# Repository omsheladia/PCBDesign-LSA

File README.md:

# PCBDesign-LSA
  Behind the Designing of the Line Sensing Array(L.S.A)

## Using kiCAD - Open Source Software
This repository contains hardware design files and datasheets for the Line Sensor Array. This project is still in development and is not ready for release yet.
Coming soon with a finalised touch.

## Features
* Detachable I.C. for easy project based modifications.
* Components can be proctured easily.
* Easy connections for output signals.
* Compact enough to fit into any project.
* Distinguished trace widths for Signal and Power Routes.
 
## Uses
* Obstacle detection on a clear path.
* Line Following.
* Distinguish Colours on a path.

## Components Used
Component | Description
--------- | -----------
LM324 I.C. | Op-Amp I.C.
Photodiode | Absorb light
Resistor | Limit Current
LED | Emit Light
FRC Connector | Connect PCB with other circuits
14 Pin I.C. Socket | Plug LM324 I.C.
  
## Tools:
To view/modify the files from this repository, install KiCAD from: https://kicad.org

## Layout

## Plots

### Front View 

### Back View

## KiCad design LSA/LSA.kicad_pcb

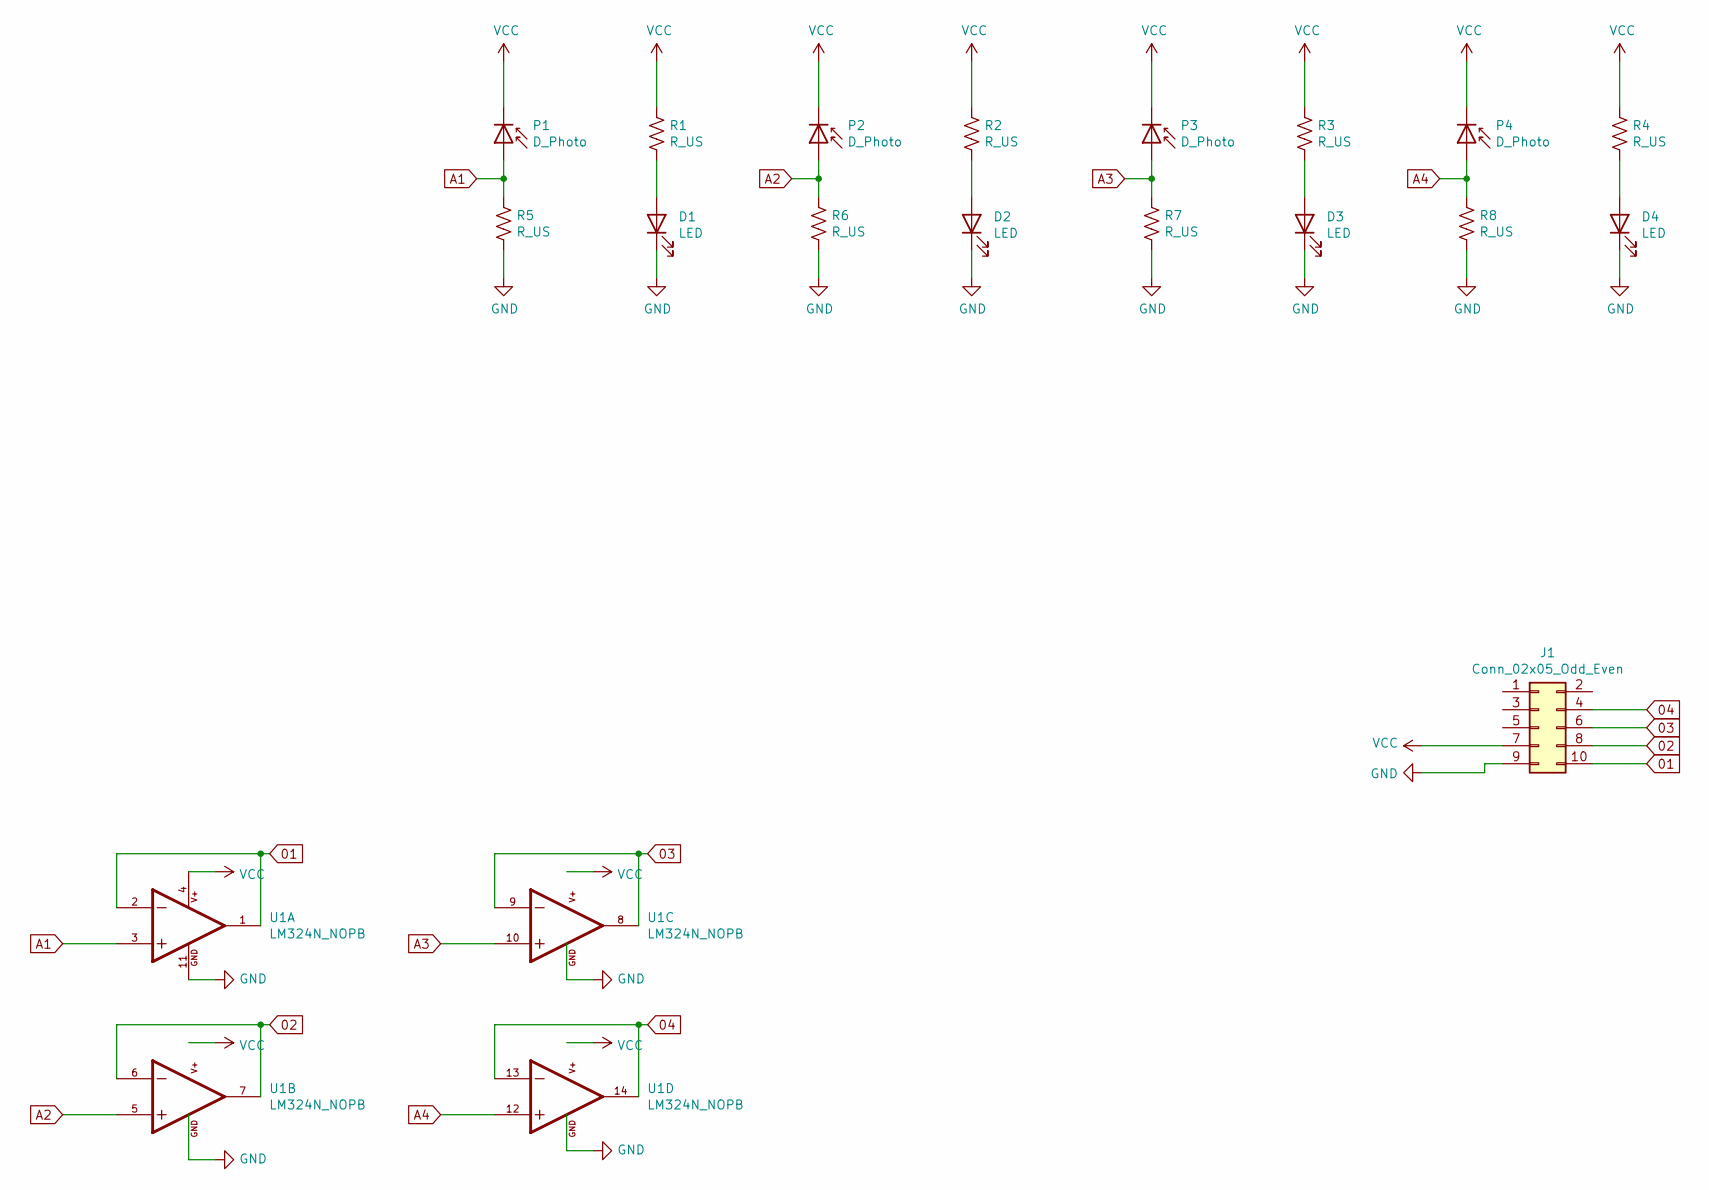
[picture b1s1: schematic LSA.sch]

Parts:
D1, D2, D3, D4: LED; LED_D3.0mm_FlatTop
J1: Conn_02x05_Odd_Even; IDC-Header_2x05_P2.54mm_Vertical
P1, P2, P3, P4: D_Photo; Osram_DIL2_4.3x4.65mm_P5.08mm
R1, R2, R3, R4, R5, R6, R7, R8: R_US; R_Axial_DIN0204_L3.6mm_D1.6mm_P7.62mm_Horizontal
U1: LM324N_NOPB; DIP825W47P254L1917H533Q14; PARTREV D

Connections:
01: J1.10, U1.1, U1.2
02: J1.8, U1.6, U1.7
03: J1.6, U1.8, U1.9
04: J1.4, U1.13, U1.14
A1: P1.2 (A), R5.1, U1.3
A2: P2.2 (A), R6.1, U1.5
A3: P3.2 (A), R7.1, U1.10
A4: P4.2 (A), R8.1, U1.12
GND: D1.1 (K), D2.1 (K), D3.1 (K), D4.1 (K), J1.9, R5.2, R6.2, R7.2, R8.2, U1.11
unnamed: D1.2 (A), R1.2
unnamed: D2.2 (A), R2.2
unnamed: D3.2 (A), R3.2
unnamed: D4.2 (A), R4.2
VCC: J1.7, P1.1 (K), P2.1 (K), P3.1 (K), P4.1 (K), R1.1, R2.1, R3.1, R4.1, U1.4

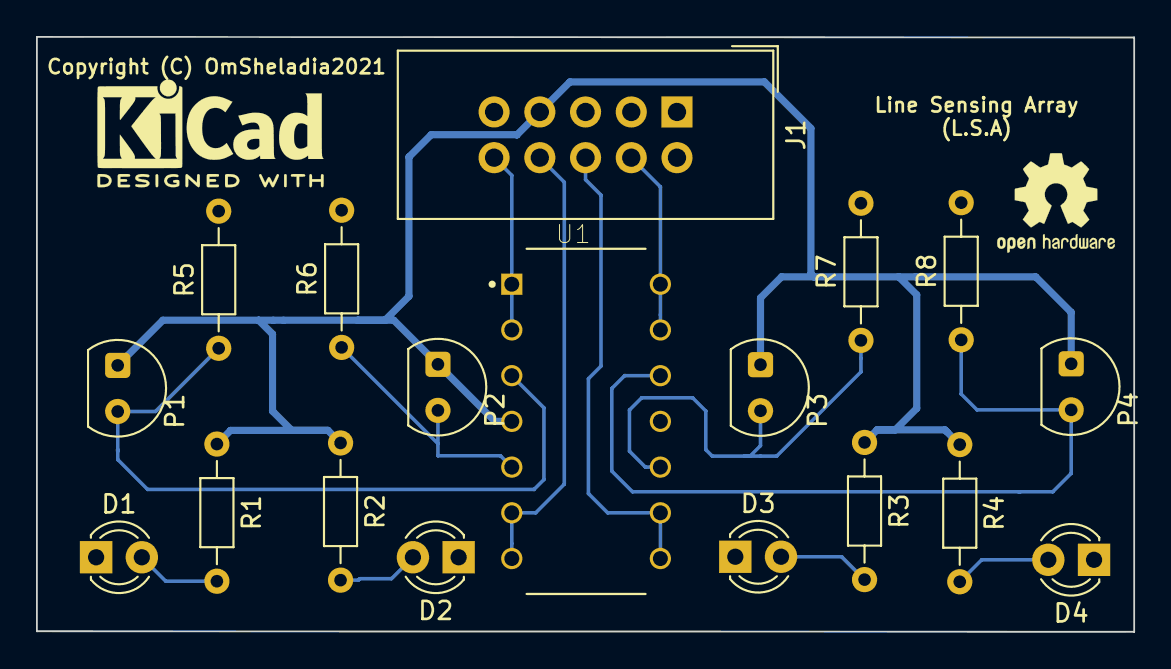
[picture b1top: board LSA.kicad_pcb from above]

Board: 2 copper layers, 61.0 x 33.1 mm, 18 parts (0 on the bottom side), 14 nets.

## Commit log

2021-06-22 almost done
2021-06-24 Added Components, Layout and Back View.
2021-06-24 KiCad Resources Added
2021-06-28 Update README.md
    Images added properly!
2021-07-13 Assets and KiCad Files added
2021-07-13 deleted extra file
2021-07-13 F Cu layer changed colour layout
2021-07-13 updated Front view

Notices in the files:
LSA/LSA.kicad_pcb:
Copyright (C) OmSheladia2021
